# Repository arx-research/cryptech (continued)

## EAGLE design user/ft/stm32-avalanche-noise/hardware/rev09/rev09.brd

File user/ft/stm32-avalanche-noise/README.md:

STM32 avalanche noise entropy source
====================================

This is an open source and open hardware entropy source, using an
STM32 microcontroller to gather entropy from a common avalanche
noise circuit.

A special thanks goes to Benedikt Stockebrand who designed the circuit
and the currently used core extraction algorithm in his ARRGH project.

  http://www.stepladder-it.com/Downloads/arrgh-0.2.1alpha.txz

Copyrights
==========

The license for all work done on this in the CrypTech project is a
3-clause BSD license (see LICENSE.txt for details). Some files have
been generated using the STMicroelectronics initialization code
generator STM32CubeMX and thus have additional copyright header(s).

The "Noise generator" and "Amplifier" parts of the circuit diagram are
copied from the ARRGH project. ARRGH copyright statement is included
in LICENSE.txt.

A stripped down copy of the ARM CMSIS library version 3.20 is included
in the Drivers/CMSIS/ directory. Unused parts (and documentation etc.)
have been removed, but every attempt have been made to keep any
licensing information intact. See in particular the file
Drivers/CMSIS/CMSIS END USER LICENCE AGREEMENT.pdf.

A full copy of the STM32F4xx HAL Drivers is included in the
Drivers/STM32F4xx_HAL_Driver/ directory.

Building
========

The following packages need to be installed (on Ubuntu 14.04):

  apt-get install gcc-arm-none-eabi gdb-arm-none-eabi openocd

XXX not sure this is the complete set, if you find that you need
additional packages please let me know. See e-mail address at the bottom.

To build the source code, issue "make" from the top level directory
(where this file is). The first time, this will build the complete STM
CMSIS library. A subsequent "make clean" will *not* clean away the CMSIS
library, but a "make really-clean" will.

Installing
==========

Do "make flash-target" from the top level directory (where this file is)
to build the firmware for the application selected in the top level
Makefile and flash it into the microcontroller. See the section STLINK
below for information about the actual hardware programming device needed.

Using
=====

The microcontroller code can currently run in one of two modes, set
statically at the beginning of main(): MODE_DELTAS and MODE_ENTROPY.

MODE_ENTROPY is the default, and means the microcontroller will send
entropy as binary data as fast as it can get it, which is about 24 kB/s
in the current version of hardware and software. To get some entropy
and perform rudimentary analysis of it, and assuming USB is used and
the device was enumerated as ttyUSB0, do

  ldattach -8 -n -1 -s 460800 tty /dev/ttyUSB0
  echo > /dev/ttyUSB0
  cat /dev/ttyUSB0 | rngtest -c 10
  cat /dev/ttyUSB0 | head -c 100000 | ent

For Raspberry-Pi, follow any of the guides on the internet for how to
enable the serial port on the GPIO pin header and then try

  ldattach -s 115200 -8 -n -1 tty /dev/ttyAMA0
  echo > /dev/ttyAMA0
  cat /dev/ttyAMA0 | rngtest -c 10
  cat /dev/ttyAMA0 | head -c 100000 | ent

(the baud rate used with the R-Pi could probably be increased with a
little hardware debugging effort).

Which UART on the board that will receive the entropy is controlled
by the sending of a newline to the UART ('echo > /dev/ttyUSB0' and
'echo > /dev/ttyAMA0' in the examples above). The power on default is
the USB UART.

MODE_DELTAS is a quality assurance mode, and outputs the raw Timer IC
values captured for analysis. The stand alone program in src/delta16/
parses the data format used by MODE_DELTAS and can convert it to
something you can analyse. More about how to do that later.

Contents
========

This documentation needs to be improved, but here are some quick notes:

Hardware design (Eagle and PDF files) are in hardware/rev09/

The firmware to extract entropy from this hardware is in src/entropy/

There are additional firmwares to aid in debugging any hardware issues
in src/led-test/ and src/uart-test/

Hardware
========

The avalanche noise circuit was first implemented using a NUCLEO-F401RE
evaluation board that has an STM32F401RET6 MCU. Because of human error,
the STM32F401RBT6 was used when assembling rev08 and rev09 boards. This
chip has less flash and RAM, so some region mappings had to change.

MCU dependant parameters are found in the top level common.mk near the
top, read the comments regarding STDPERIPH_SETTINGS, MCU_LINKSCRIPT and
SRCS.

STLINK
======
To program the MCU, an STLINK adapter is used. The cheapest way to get
one is to buy an evaluation board with an STLINK integrated, and pinouts
to program external chips. All the evaluation boards I've encountered
from STM has this ability. I'm using an STLINK from an STM32F4DISCOVERY
board, but the even cheaper NUCLEO-F401RE should work too. The NUCLEO
one has a STLINK v2.1 which is probably, but not necessarily, supported
by the OpenOCD version in your Linux distribution (as of end of 2014).

The STLINK programming pins are the 1+4 throughole pads above the ARM
on the circuit board. See the schematics for details, but the pinout
from left to right (1, space, 4) of rev09 is

  NRST, space, CLK, IO, GND, VCC

Debugging the firmware
======================

This site shows several ways to use various debuggers to debug the
firmware in an STM32:

  http://fun-tech.se/stm32/OpenOCD/gdb.php

I've only managed to get the most basic text line gdb to work,
something along these lines:

1) Start OpenOCD server (with a configuration file for your type of STLINK
   adapter)

   $ openocd -f /usr/share/openocd/scripts/board/stm32f4discovery.cfg

2) Connect to the OpenOCD server and re-flash already compiled firmware:

   $ telnet localhost 4444
   reset halt
   flash probe 0
   stm32f2x mass_erase 0
   flash write_bank 0 /path/to/main.bin 0
   reset halt

3) Start GDB and have it connect to the OpenOCD server:

   $ arm-none-eabi-gdb --eval-command="target remote localhost:3333" main.elf

---
Fredrik Thulin <fredrik@thulin.net>, for the
CrypTech project <https://cryptech.is/>
2015-01-14

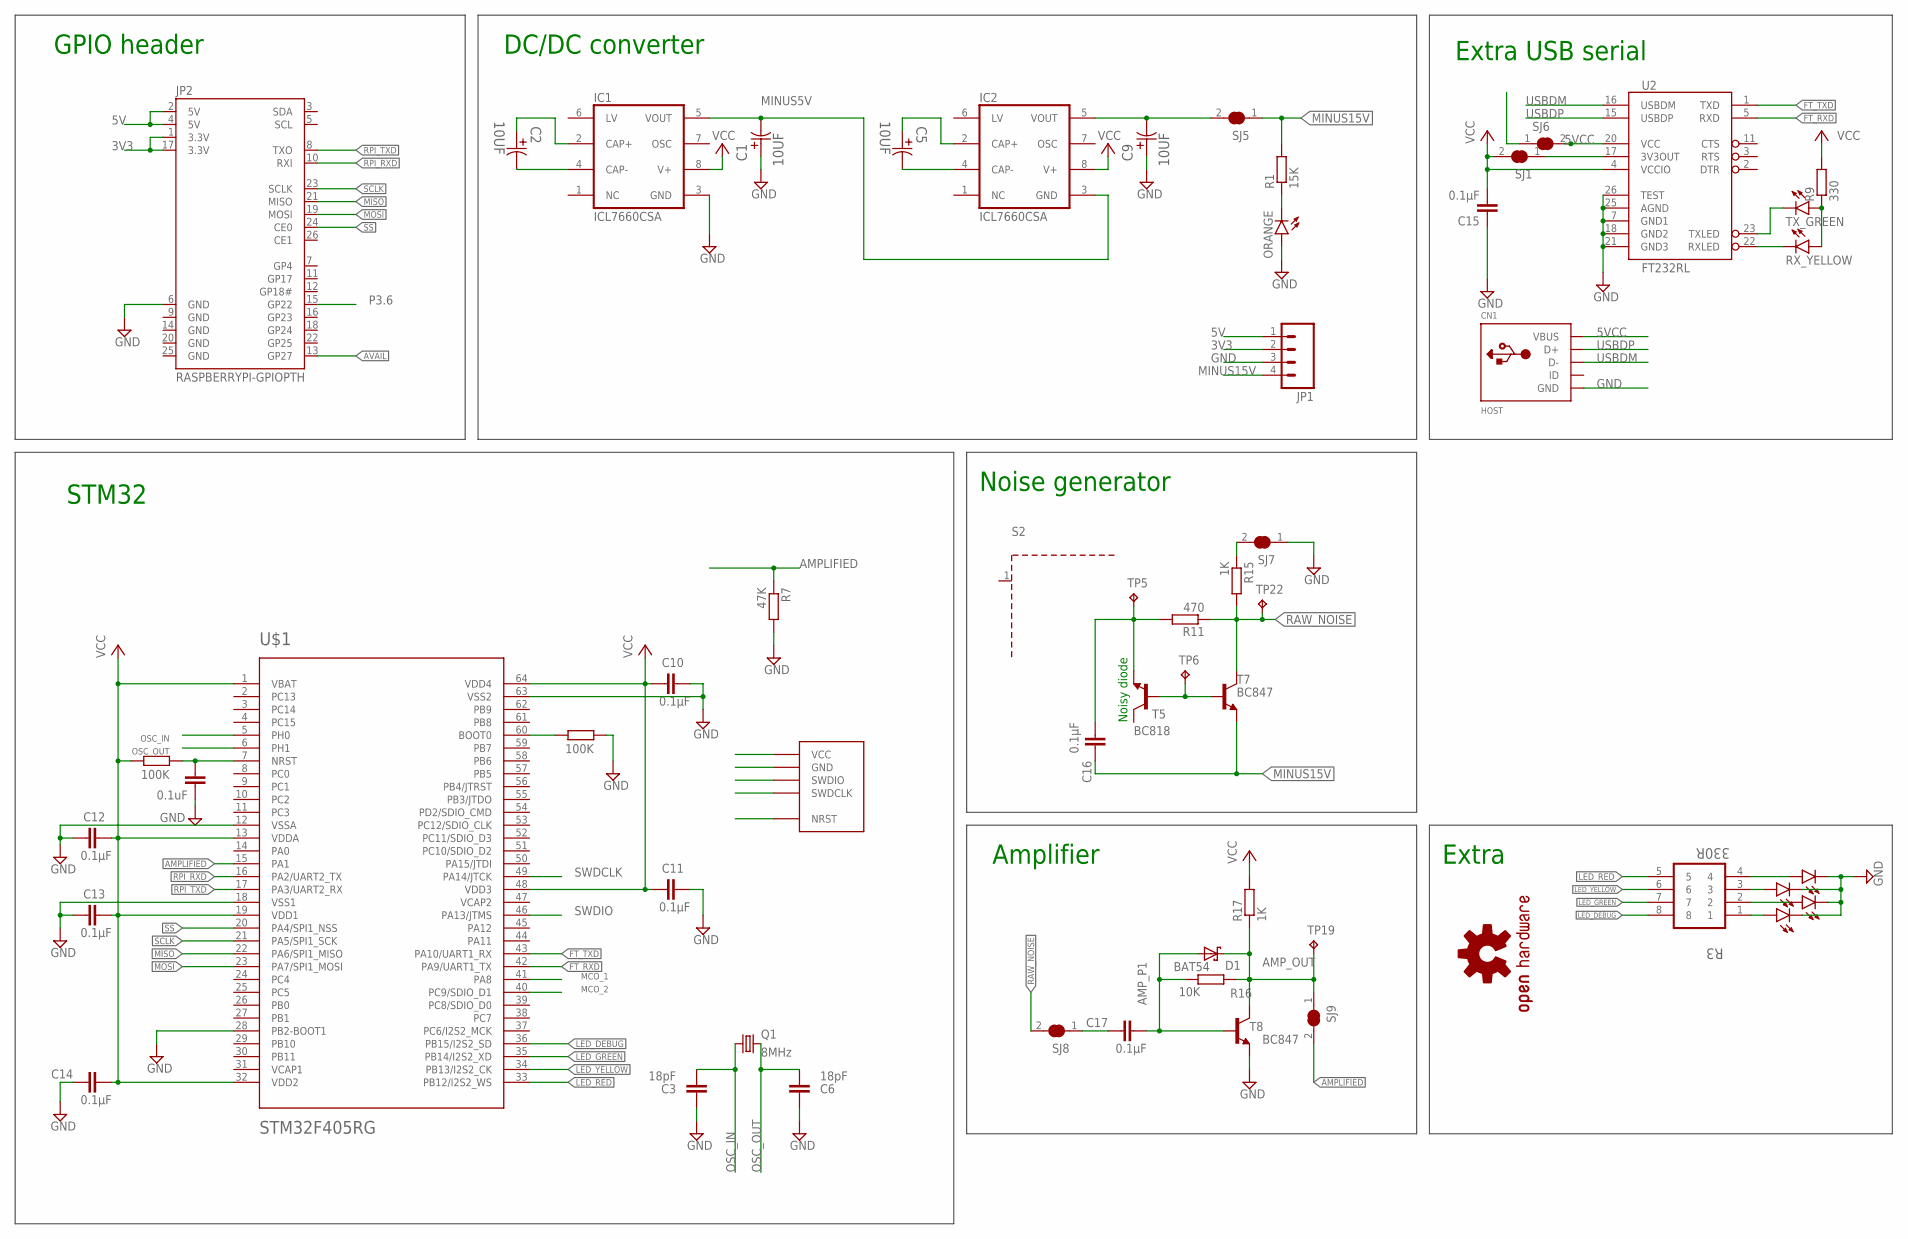
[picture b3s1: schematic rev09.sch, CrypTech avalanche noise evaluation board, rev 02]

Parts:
C1, C2, C5, C9: 10UF; CAPAE530X610N
C3, C6: 18pF; C0603
C4: 0.1uF; C0603
C10, C11, C12, C13, C14, C15, C16, C17: 0.1µF; C0603
CN1: HOST; USB-MINIB
D1: BAT54; SOT23
IC1, IC2: ICL7660CSA; SO08
JP1: M04LOCK; 1X04_LOCK
JP2: RASPBERRYPI-GPIOPTH; 2X13-SHROUDED
LED5, LED6, LED7, LED8: LED0603; LED-0603
LOGO1: OSHW-LOGOL; OSHW-LOGO-L
ORANGE: LED0603; LED-0603
Q1: 8MHz; CTS406
R1: 15K; R0603
R2, R8: 100K; R0603
R3: 330R; RESCAXE80P320X160X60-8N
R7: 47K; R0603
R9: 330; R0603
R11: 470; R0603
R15, R17: 1K; R0603
R16: 10K; R0603
RX_YELLOW: LED0603; LED-0603
S2: WE-SHC_36103205
SJ1, SJ5, SJ6, SJ7, SJ8, SJ9: SOLDERJUMPER_CLOSED; SOLDERJUMPER_CLOSEDWIRE
T5: BC818; SOT23-BEC
T7, T8: BC847; SOT23
TP5, TP6, TP19, TP22: TPB1,27; B1,27
TX_GREEN: LED0603; LED-0603
U2: FT232RL; SSOP28DB
U$1: STM32F405RG; TQFP64
U$2: STM32-SWD; 100MIL_THT

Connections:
3V3: C10.1, C11.1, C12.2, C13.2, C14.2, C15.2, JP1.2, JP2.1 (3.3V), JP2.17 (3.3V), R2.2, R17.2, SJ1.2, U2.4 (VCCIO), U$1.1 (VBAT), U$1.13 (VDDA), U$1.19 (VDD1), U$1.32 (VDD2), U$1.48 (VDD3), U$1.64 (VDD4), U$2.P$VCC (VCC)
3V3OUT: R9.2, SJ1.1, U2.17 (3V3OUT)
5V: IC1.8 (V+), IC2.8 (V+), JP1.1, JP2.2 (5V), JP2.4 (5V), SJ6.1
5VCC: CN1.VBUS, SJ6.2, U2.20 (VCC)
AMPLIFIED: R7.1, SJ9.2, U$1.15 (PA1)
AMP_OUT: D1.3 (C), R16.2, R17.1, SJ9.1, T8.3 (C), TP19.TP
AMP_P1: C17.2, D1.1 (A), R16.1, T8.1 (B)
AVAIL: JP2.13 (GP27)
BOOT0: R8.2, U$1.60 (BOOT0)
FT_RXD: U2.5 (RXD), U$1.42 (PA9/UART1_TX)
FT_TXD: U2.1 (TXD), U$1.43 (PA10/UART1_RX)
GND: C1.1, C3.1, C4.1, C6.1, C9.1, C10.2, C11.2, C12.1, C13.1, C14.1, C15.1, CN1.GND, IC1.3 (GND), JP1.3, JP2.6 (GND), JP2.9 (GND), JP2.14 (GND), JP2.20 (GND), JP2.25 (GND), LED5.C, LED6.C, LED7.C, LED8.C, ORANGE.A, R7.2, R8.1, S2.1, SJ7.1, T8.2 (E), U2.7 (GND1), U2.18 (GND2), U2.21 (GND3), U2.25 (AGND), U2.26 (TEST), U$1.12 (VSSA), U$1.18 (VSS1), U$1.28 (PB2-BOOT1), U$1.63 (VSS2), U$2.P$GND (GND)
LED_DEBUG: R3.8, U$1.36 (PB15/I2S2_SD)
LED_GREEN: R3.7, U$1.35 (PB14/I2S2_XD)
LED_RED: R3.5, U$1.33 (PB12/I2S2_WS)
LED_YELLOW: R3.6, U$1.34 (PB13/I2S2_CK)
MCO_1: U$1.41 (PA8)
MCO_2: U$1.40 (PC9/SDIO_D1)
MINUS5V: C1.2, IC1.5 (VOUT), IC2.3 (GND)
MINUS15V: C16.1, JP1.4, R1.2, SJ5.1, T7.2 (E)
MINUS15V_1: C9.2, IC2.5 (VOUT), SJ5.2
MISO: JP2.21 (MISO), U$1.22 (PA6/SPI1_MISO)
MOSI: JP2.19 (MOSI), U$1.23 (PA7/SPI1_MOSI)
unnamed: C5.2, IC2.4 (CAP-)
unnamed: C2.2, IC1.4 (CAP-)
unnamed: C2.1, IC1.2 (CAP+)
unnamed: ORANGE.C, R1.1
unnamed: C5.1, IC2.2 (CAP+)
unnamed: RX_YELLOW.C, U2.22 (RXLED)
unnamed: TX_GREEN.C, U2.23 (TXLED)
unnamed: R9.1, RX_YELLOW.A, TX_GREEN.A
unnamed: R15.1, SJ7.2
unnamed: LED5.A, R3.4
unnamed: LED6.A, R3.3
unnamed: LED7.A, R3.2
unnamed: LED8.A, R3.1
NOISE_IN1: C16.2, R11.2, T5.E, TP5.TP
NOISE_OUT1: T5.B, T7.1 (B), TP6.TP
NRST: C4.2, R2.1, U$1.7 (NRST), U$2.P$NRST (NRST)
OSC_IN: C3.2, Q1.1, U$1.5 (PH0)
OSC_OUT: C6.2, Q1.3 (2), U$1.6 (PH1)
P3.6: JP2.15 (GP22)
RAW_NOISE: R11.1, R15.2, SJ8.2, T7.3 (C), TP22.TP
RAW_NOISE1: C17.1, SJ8.1
RPI_RXD: JP2.10 (RXI), U$1.16 (PA2/UART2_TX)
RPI_TXD: JP2.8 (TXO), U$1.17 (PA3/UART2_RX)
SCLK: JP2.23 (SCLK), U$1.21 (PA5/SPI1_SCK)
SS: JP2.24 (CE0), U$1.20 (PA4/SPI1_NSS)
SWDCLK: U$1.49 (PA14/JTCK), U$2.P$SWDCLK (SWDCLK)
SWDIO: U$1.46 (PA13/JTMS), U$2.P$SWDIO (SWDIO)
USBDM: CN1.D-, U2.16 (USBDM)
USBDP: CN1.D+, U2.15 (USBDP)

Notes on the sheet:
GPIO header
DC/DC converter
STM32
Extra
Extra USB serial
Noise generator
Amplifier
Noisy diode

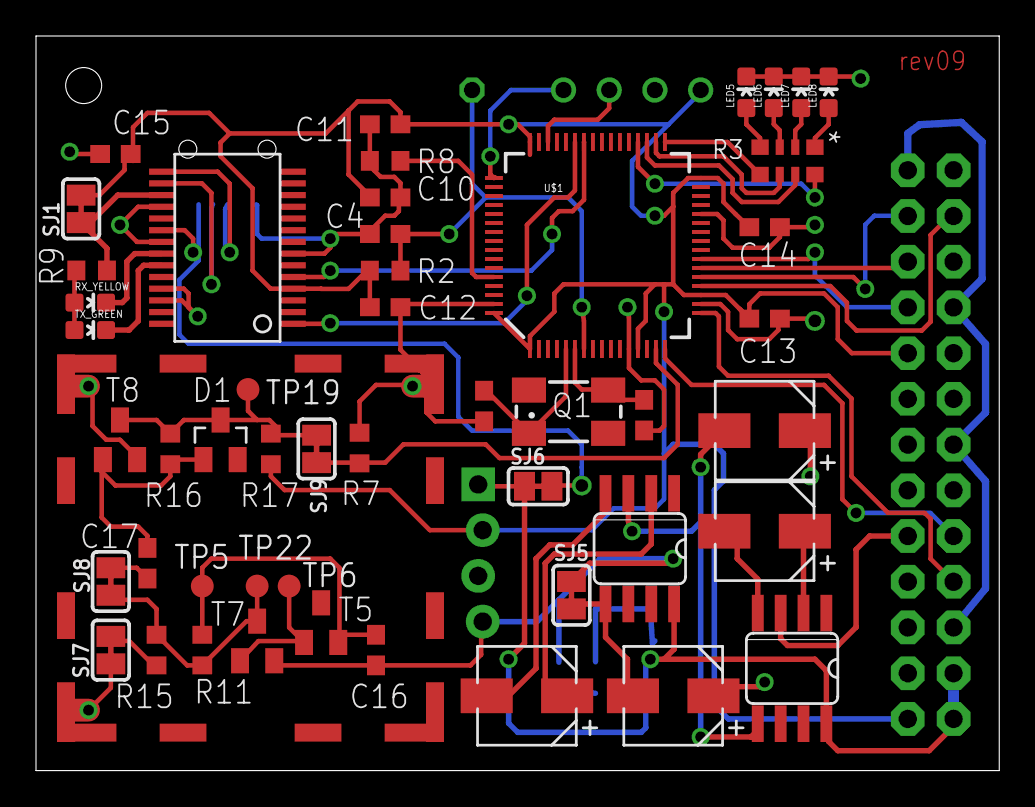
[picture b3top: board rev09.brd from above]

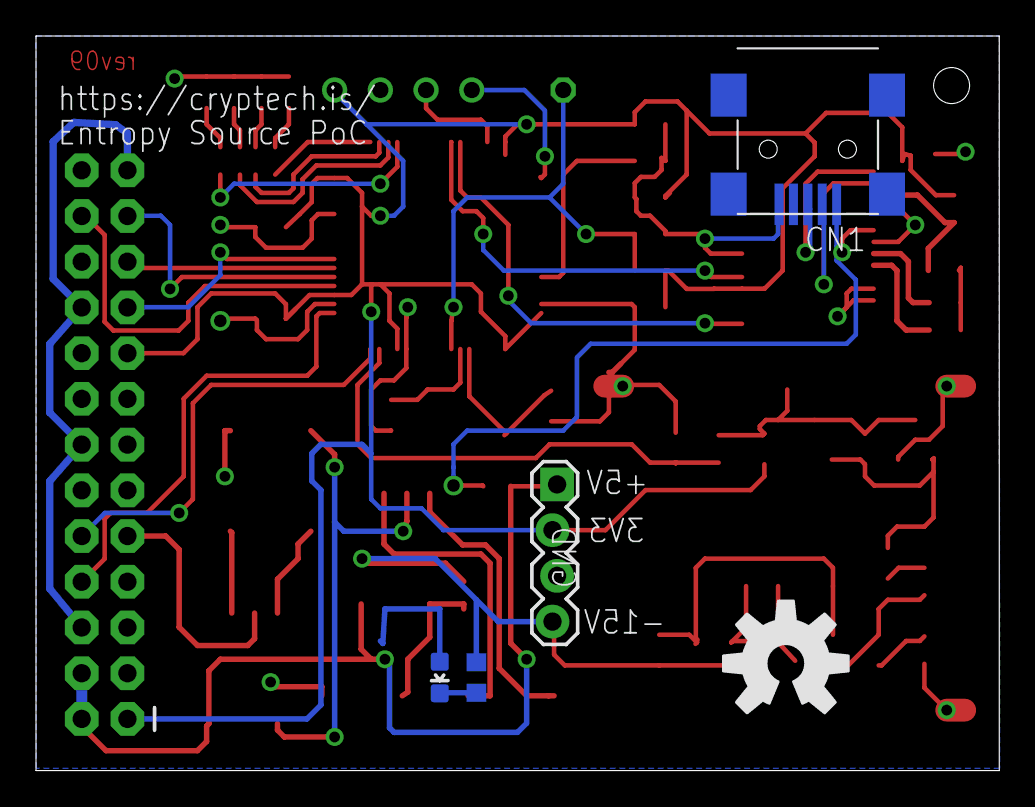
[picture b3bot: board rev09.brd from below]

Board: 2 copper layers, 53.5 x 40.8 mm, 57 parts (6 on the bottom side), 48 nets.

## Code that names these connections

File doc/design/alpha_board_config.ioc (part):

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Mcu.Name=STM32F439B(G-I)Tx
Mcu.Package=LQFP208
Mcu.UserName=STM32F439BITx
PA10.Mode=Asynchronous
PA10.Signal=USART1_RX
PA2.Mode=Asynchronous
PA2.Signal=USART2_TX
PA3.Mode=Asynchronous
PA3.Signal=USART2_RX
PA5.Mode=Full_Duplex_Master
PA5.Signal=SPI1_SCK
PA6.Mode=Full_Duplex_Master
PA6.Signal=SPI1_MISO
PA7.Mode=Full_Duplex_Master
PA7.Signal=SPI1_MOSI
PA9.Mode=Asynchronous
PA9.Signal=USART1_TX
PB10.Mode=Asynchronous
PB10.Signal=USART3_TX
PB11.Mode=Asynchronous
PB11.Signal=USART3_RX
PB13.Mode=Full_Duplex_Master
PB13.Signal=SPI2_SCK
PB6.Mode=I2C
PB6.Signal=I2C1_SCL
PB7.Mode=I2C
PB7.Signal=I2C1_SDA
PC0.Signal=FMC_SDNWE
PC10.Mode=mmc_4_bits_Wide_bus
PC10.Signal=SDIO_D2
PC11.Mode=mmc_4_bits_Wide_bus
PC11.Signal=SDIO_D3
PC12.Mode=mmc_4_bits_Wide_bus
PC12.Signal=SDIO_CK
PC2.Mode=Full_Duplex_Master
PC2.Signal=SPI2_MISO
PC3.Mode=Full_Duplex_Master
PC3.Signal=SPI2_MOSI
PC8.Mode=mmc_4_bits_Wide_bus
PC8.Signal=SDIO_D0
PC9.Mode=mmc_4_bits_Wide_bus
PC9.Signal=SDIO_D1
PD0.Signal=FMC_D2_DA2
PD1.Signal=FMC_D3_DA3
PD10.Signal=FMC_D15_DA15
PD11.Signal=FMC_A16_CLE
PD12.Signal=FMC_A17_ALE
PD13.Signal=FMC_A18
PD14.Signal=FMC_D0_DA0
PD15.Signal=FMC_D1_DA1
PD2.Mode=mmc_4_bits_Wide_bus
PD2.Signal=SDIO_CMD
PD4.Signal=FMC_NOE
PD5.Signal=FMC_NWE
PD7.Mode=NorPsramChipSelect1_1
PD7.Signal=FMC_NE1
PD8.Signal=FMC_D13_DA13
PD9.Signal=FMC_D14_DA14
PE0.Signal=FMC_NBL0
PE1.Signal=FMC_NBL1
PE10.Signal=FMC_D7_DA7
PE11.Signal=FMC_D8_DA8
PE12.Signal=FMC_D9_DA9
PE13.Signal=FMC_D10_DA10
PE14.Signal=FMC_D11_DA11
PE15.Signal=FMC_D12_DA12
PE2.Signal=FMC_A23
PE3.Signal=FMC_A19
PE4.Signal=FMC_A20
PE5.Signal=FMC_A21
PE6.Signal=FMC_A22
PE7.Signal=FMC_D4_DA4
PE8.Signal=FMC_D5_DA5
PE9.Signal=FMC_D6_DA6
PF0.Signal=FMC_A0
PF1.Signal=FMC_A1
PF11.Signal=FMC_SDNRAS
PF12.Signal=FMC_A6
PF13.Signal=FMC_A7
PF14.Signal=FMC_A8
PF15.Signal=FMC_A9
PF2.Signal=FMC_A2
PF3.Signal=FMC_A3
PF4.Signal=FMC_A4
PF5.Signal=FMC_A5
PG0.Signal=FMC_A10
PG1.Signal=FMC_A11
PG13.Signal=FMC_A24
PG14.Signal=FMC_A25
PG15.Signal=FMC_SDNCAS
PG2.Signal=FMC_A12
PG3.Signal=FMC_A13
PG4.Signal=FMC_A14_BA0
PG5.Signal=FMC_A15_BA1
PG8.Signal=FMC_SDCLK
PH10.Signal=FMC_D18
PH11.Signal=FMC_D19
PH12.Signal=FMC_D20
PH13.Signal=FMC_D21
PH14.Signal=FMC_D22
PH15.Signal=FMC_D23
PH2.Mode=SdramChipSelect1_1
PH2.Signal=FMC_SDCKE0
PH3.Mode=SdramChipSelect1_1
PH3.Signal=FMC_SDNE0
PH6.Mode=SdramChipSelect2_2
PH6.Signal=FMC_SDNE1
PH7.Mode=SdramChipSelect2_2
PH7.Signal=FMC_SDCKE1
PH8.Signal=FMC_D16
PH9.Signal=FMC_D17
PI0.Signal=FMC_D24
PI1.Signal=FMC_D25
PI10.Signal=FMC_D31
PI2.Signal=FMC_D26
PI3.Signal=FMC_D27
PI4.Signal=FMC_NBL2
PI5.Signal=FMC_NBL3
PI6.Signal=FMC_D28
PI7.Signal=FMC_D29
PI9.Signal=FMC_D30
RCC.HSE_VALUE=25000000
RCC.SYSCLKFreq_VALUE=16000000

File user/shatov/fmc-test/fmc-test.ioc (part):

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Mcu.Name=STM32F429B(E-G-I)Tx
Mcu.Package=LQFP208
Mcu.UserName=STM32F429BITx
PA13.Mode=Serial-Wire
PA13.Signal=SYS_JTMS-SWDIO
PA14.Mode=Serial-Wire
PA14.Signal=SYS_JTCK-SWCLK
PB7.Signal=FMC_NL
PD0.Signal=FMC_D2_DA2
PD1.Signal=FMC_D3_DA3
PD10.Signal=FMC_D15_DA15
PD11.Signal=FMC_A16_CLE
PD12.Signal=FMC_A17_ALE
PD13.Signal=FMC_A18
PD14.Signal=FMC_D0_DA0
PD15.Signal=FMC_D1_DA1
PD3.Signal=FMC_CLK
PD4.Signal=FMC_NOE
PD5.Signal=FMC_NWE
PD6.GPIOParameters=GPIO_PuPd,GPIO_Label,GPIO_Mode
PD6.GPIO_Label=FMC_NWAIT
PD6.GPIO_Mode=GPIO_MODE_INPUT
PD6.GPIO_PuPd=GPIO_NOPULL
PD6.Signal=GPIO_Input
PD7.Mode=NorPsramChipSelect1_1
PD7.Signal=FMC_NE1
PD8.Signal=FMC_D13_DA13
PD9.Signal=FMC_D14_DA14
PE10.Signal=FMC_D7_DA7
PE11.Signal=FMC_D8_DA8
PE12.Signal=FMC_D9_DA9
PE13.Signal=FMC_D10_DA10
PE14.Signal=FMC_D11_DA11
PE15.Signal=FMC_D12_DA12
PE3.Signal=FMC_A19
PE4.Signal=FMC_A20
PE5.Signal=FMC_A21
PE7.Signal=FMC_D4_DA4
PE8.Signal=FMC_D5_DA5
PE9.Signal=FMC_D6_DA6
PF0.Signal=FMC_A0
PF1.Signal=FMC_A1
PF12.Signal=FMC_A6
PF13.Signal=FMC_A7
PF14.Signal=FMC_A8
PF15.Signal=FMC_A9
PF2.Signal=FMC_A2
PF3.Signal=FMC_A3
PF4.Signal=FMC_A4
PF5.Signal=FMC_A5
PG0.Signal=FMC_A10
PG1.Signal=FMC_A11
PG2.Signal=FMC_A12
PG3.Signal=FMC_A13
PG4.Signal=FMC_A14_BA0
PG5.Signal=FMC_A15_BA1
PH10.Signal=FMC_D18
PH11.Signal=FMC_D19
PH12.Signal=FMC_D20
PH13.Signal=FMC_D21
PH14.Signal=FMC_D22
PH15.Signal=FMC_D23
PH8.Signal=FMC_D16
PH9.Signal=FMC_D17
PI0.Signal=FMC_D24
PI1.Signal=FMC_D25
PI10.Signal=FMC_D31
PI2.Signal=FMC_D26
PI3.Signal=FMC_D27
PI6.Signal=FMC_D28
PI7.Signal=FMC_D29
PI9.Signal=FMC_D30
RCC.HSE_VALUE=25000000
RCC.SYSCLKFreq_VALUE=180000000
RCC.SYSCLKSource=RCC_SYSCLKSOURCE_PLLCLK
board=fmc-test

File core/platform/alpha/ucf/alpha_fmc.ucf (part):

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#
NET  "gclk_pin"        LOC = "D17"  | IOSTANDARD = "LVCMOS33" ;
#
NET  "fmc_clk"         LOC = "W11"  | IOSTANDARD = "LVCMOS33" ;
NET  "fmc_ne1"         LOC = "V5"   | IOSTANDARD = "LVCMOS33" ;
NET  "fmc_noe"         LOC = "W16"  | IOSTANDARD = "LVCMOS33" ;
NET  "fmc_nwe"         LOC = "AA6"  | IOSTANDARD = "LVCMOS33" ;
NET  "fmc_nl"          LOC = "W17"  | IOSTANDARD = "LVCMOS33" ;
NET  "fmc_nwait"       LOC = "Y6"   | IOSTANDARD = "LVCMOS33" | SLEW = "FAST" | DRIVE = 8;
#
NET  "fmc_a<0>"        LOC = "Y17"  | IOSTANDARD = "LVCMOS33" ;
NET  "fmc_a<1>"        LOC = "AB16" | IOSTANDARD = "LVCMOS33" ;
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
NET  "mkm_sclk"        LOC = "V3"   | IOSTANDARD = "LVCMOS33" ;
NET  "mkm_cs_n"        LOC = "W2"   | IOSTANDARD = "LVCMOS33" ;
NET  "mkm_di"          LOC = "W1"   | IOSTANDARD = "LVCMOS33" ; # MKM_FPGA_MOSI
NET  "mkm_do"          LOC = "Y1"   | IOSTANDARD = "LVCMOS33" ; # MKM_FPGA_MISO

#-------------------------------------------------------------------------------
# FMC Input Timing
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
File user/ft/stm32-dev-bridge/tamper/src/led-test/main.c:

#include <inttypes.h>
#include <avr/io.h>
//#include <util/delay.h>

#include "iotn828.h"

#define AVR_LED4 PORTA4  /* RED */
#define AVR_LED3 5  /* YELLOW */
#define AVR_LED2 6  /* GREEN */
#define AVR_LED1 7  /* BLUE */


void main() {
  int i;
  uint8_t j = 0;

  /* Enable PA4 output */
  //  DDRA |= (1 << AVR_LED4) | (1 << AVR_LED3) | (1 << AVR_LED2) | (1 << AVR_LED1);
  DDRA |= 0xf0;

  //PORTA = 0;
  while (1) {
    PORTA = (PORTA & 0x0f) | ((j++<<4) & 0xf0);
    //PORTA ^= (1 << AVR_LED1);
    //PORTA = j++;
    for (i = 0; i < 10000; i++) { ; }
    //_delay_ms (100);
  }
}

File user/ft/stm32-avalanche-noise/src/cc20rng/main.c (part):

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  /* Toggle GREEN LED to show we've initialized */
  {
    for (i = 0; i < 10; i++) {
      HAL_GPIO_TogglePin(LED_PORT, LED_GREEN);
      HAL_Delay(125);
    }
  }
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   */
  while (1) {
    if (! (block_counter % 1000)) {
      HAL_GPIO_TogglePin(LED_PORT, LED_YELLOW);
    }

    if (! block_counter) {
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
    if (UartReady != SET) {
      /* Failed to send, turn on RED LED for one second */
      HAL_GPIO_WritePin(LED_PORT, LED_RED, GPIO_PIN_SET);
      HAL_Delay(1000);
      HAL_GPIO_WritePin(LED_PORT, LED_RED, GPIO_PIN_RESET);
    }

    /* Check for UART change request */
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void Error_Handler(void)
{
  /* Turn on RED LED and then loop indefinitely */
  HAL_GPIO_WritePin(LED_PORT, LED_RED, GPIO_PIN_SET);
  while(1) { ; }
}

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
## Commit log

2018-10-22 Usage instructions for cloning submodules from CrypTech
2018-10-22 adding x25519 submodule
2018-10-22 modifying directory hierarchy
2018-10-22 updating folder hierarchy
2018-10-23 updating broken submodule paths to point at the correct repos
2018-10-25 removing scaffolding file
